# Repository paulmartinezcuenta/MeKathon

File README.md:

# 🤖 MeKathon - Autonomous Mini Sumo 10x10

Official team repository for the development of a fully autonomous Mini Sumo robot, designed to compete under the official rules of the 10x10 cm category.

## 📂 Project Structure

* 📁 [**`3D_Design/`**](./3D_Design): CAD models for the chassis, front scoop, and structural components.
* 📁 [**`PCB/`**](./PCB): Schematic design and PCB routing (KiCad).
* 📁 [**`Firmware/`**](./Firmware): C source code for control logic, sensor reading, and combat strategy implementation on the ESP32.
* 📁 [**`Docs/`**](./Docs): Official rules, component datasheets, and architecture diagrams.

## 🛠️ Engineering Specifications

| Subsystem | Description |
| :--- | :--- |
| **Microcontroller** | ESP32 |
| **Target Sensors** | [Specify model, e.g., Sharp IR / LiDAR] |
| **Edge Sensors** | [Specify model, e.g., QTR] |
| **Actuators** | High-speed micro metal gearmotors |
| **Power Supply** | LiPo Battery [e.g., 2S 7.4V] |

## 👥 Development Team
* **Paul** - Hardware & PCB Design
* **Miguel** - Structural 3D Design
* **Isaias** - Firmware Development
* **Alberto** - Firmware Development

---
*Designed for the MeKathon 2026 competition.*

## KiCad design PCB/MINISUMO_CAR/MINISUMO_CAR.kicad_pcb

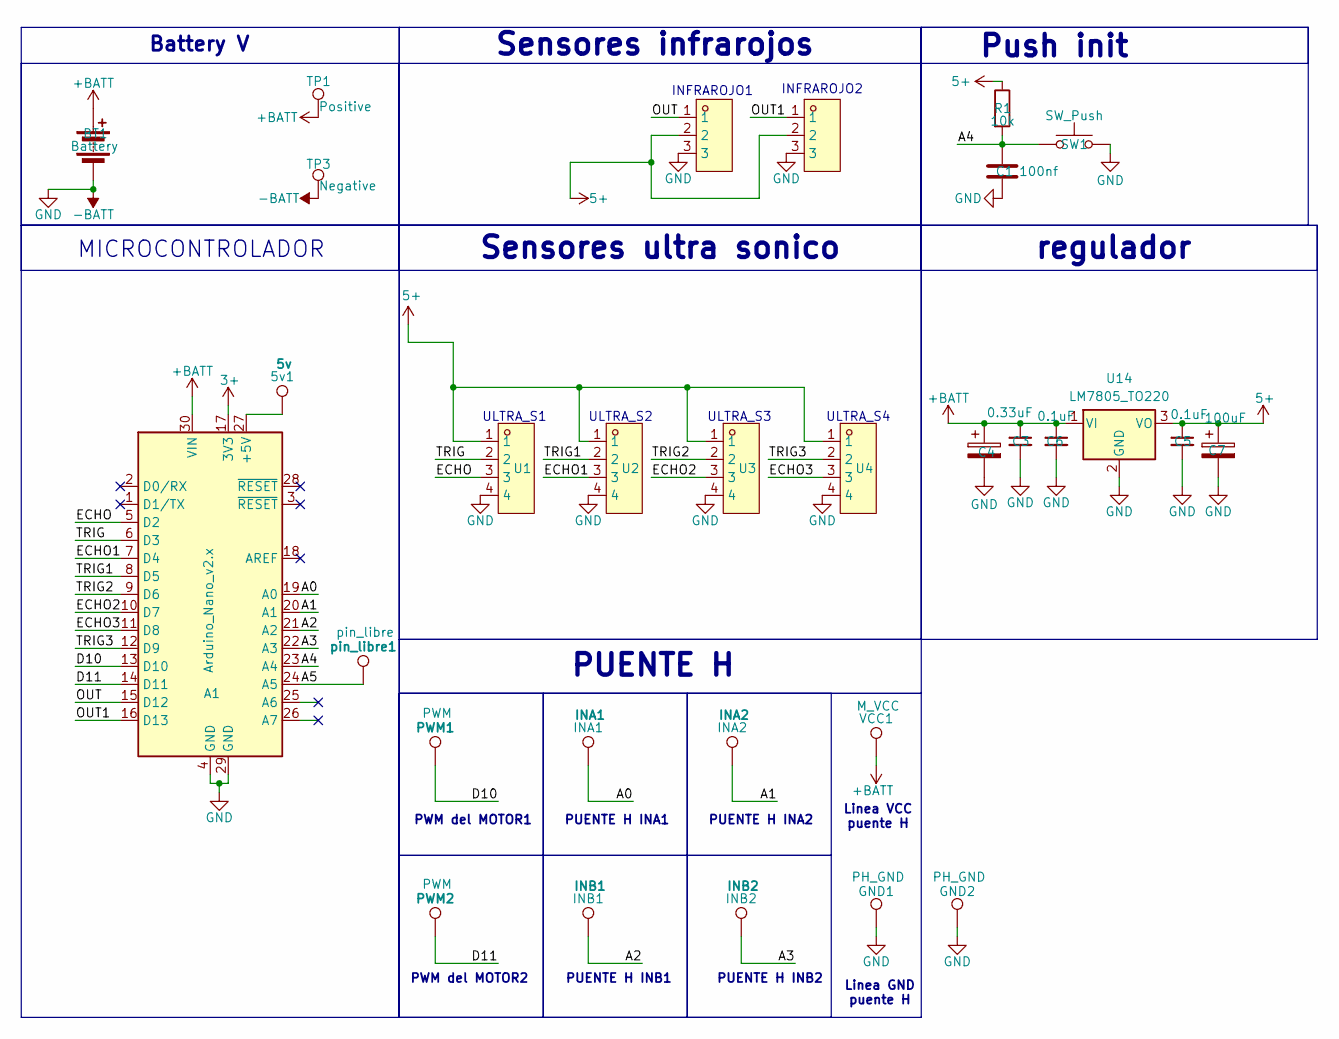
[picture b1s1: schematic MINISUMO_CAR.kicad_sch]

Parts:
5v1: 5v; PinHeader_1x01_P2.00mm_Vertical
A1: Arduino_Nano_v2.x; Arduino_Nano
BT1: Battery
C1: 100nf; C_0805_2012Metric
C3: 0.33uF; C_0805_2012Metric
C4: 470uf; CP_Elec_10x10.5
C5, C6: 0.1uF; C_0805_2012Metric
C7: 100uF; CP_Elec_6.3x7.7
GND1, GND2: PH_GND; PinHeader_1x01_P2.00mm_Vertical
INA1: INA1; PinHeader_1x01_P2.00mm_Vertical
INA2: INA2; PinHeader_1x01_P2.00mm_Vertical
INB1: INB1; PinHeader_1x01_P2.00mm_Vertical
INB2: INB2; PinHeader_1x01_P2.00mm_Vertical
PWM1, PWM2: PWM; PinHeader_1x01_P2.00mm_Vertical
R1: 10k; R_0805_2012Metric_Pad1.20x1.40mm_HandSolder
SW1: SW_Push; SW_PUSH_6mm_H5mm
TP1: Positive; TestPoint_THTPad_3.0x3.0mm_Drill1.5mm
TP3: Negative; TestPoint_THTPad_3.0x3.0mm_Drill1.5mm
U1, U2, U3, U4: XY-XHB2.54-4A11; HDR-TH_4P-P2.50-V-F-2; MPN XY-XHB2.54-4A11; LCSC Part C19271388
U5, U6: XY-XHB2.54-3A11; CONN-TH_3P-P2.50_XY-XHB2.54-3A11; MPN XY-XHB2.54-3A11; LCSC Part C19271387
U14: LM7805_TO220; TO-220-3_Vertical
VCC1: M_VCC; PinHeader_1x01_P2.00mm_Vertical
pin_libre1: pin_libre; PinHeader_1x01_P2.00mm_Vertical

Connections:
3+: A1.17 (3V3)
5+: C5.1, C7.1, R1.1, U1.1, U2.1, U3.1, U4.1, U5.2, U6.2, U14.3 (VO)
+BATT: A1.30 (VIN), BT1.1 (+), C3.1, C4.1, C6.1, TP1.1 (1_1), U14.1 (VI), VCC1.1 (1_1)
-BATT: A1.4 (GND), A1.29 (GND), BT1.2 (-), C1.2, C3.2, C4.2, C5.2, C6.2, C7.2, GND1.1 (1_1), GND2.1 (1_1), SW1.2, TP3.1 (1_1), U1.4, U2.4, U3.4, U4.4, U5.3, U6.3, U14.2 (GND); also elsewhere on the board
/A0: A1.19 (A0), INA1.1 (1_1)
/A1: A1.20 (A1), INA2.1 (1_1)
/A2: A1.21 (A2), INB1.1 (1_1)
/A3: A1.22 (A3), INB2.1 (1_1)
/A4: A1.23 (A4), C1.1, R1.2, SW1.1
/A5: A1.24 (A5), pin_libre1.1 (1_1)
/D10: A1.13 (D10), PWM1.1 (1_1)
/D11: A1.14 (D11), PWM2.1 (1_1)
/ECHO: A1.5 (D2), U1.3
/ECHO1: A1.7 (D4), U2.3
/ECHO2: A1.10 (D7), U3.3
/ECHO3: A1.11 (D8), U4.3
/OUT: A1.15 (D12), U5.1
/OUT1: A1.16 (D13), U6.1
/TRIG: A1.6 (D3), U1.2
/TRIG1: A1.8 (D5), U2.2
/TRIG2: A1.9 (D6), U3.2
/TRIG3: A1.12 (D9), U4.2
unnamed: 5v1.1 (1_1), A1.27 (+5V)

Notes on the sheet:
Sensores ultra sonico
ULTRA_S4
ULTRA_S1
PUENTE H
PUENTE H INB1
regulador
Battery V
Sensores infrarojos
INFRAROJO1
PUENTE H INA2
Linea GND puente H
PUENTE H INA1
ULTRA_S2
ULTRA_S3
Linea VCC puente H
Push init
INFRAROJO2
MICROCONTROLADOR
PWM del MOTOR2
PWM del MOTOR1
PUENTE H INB2

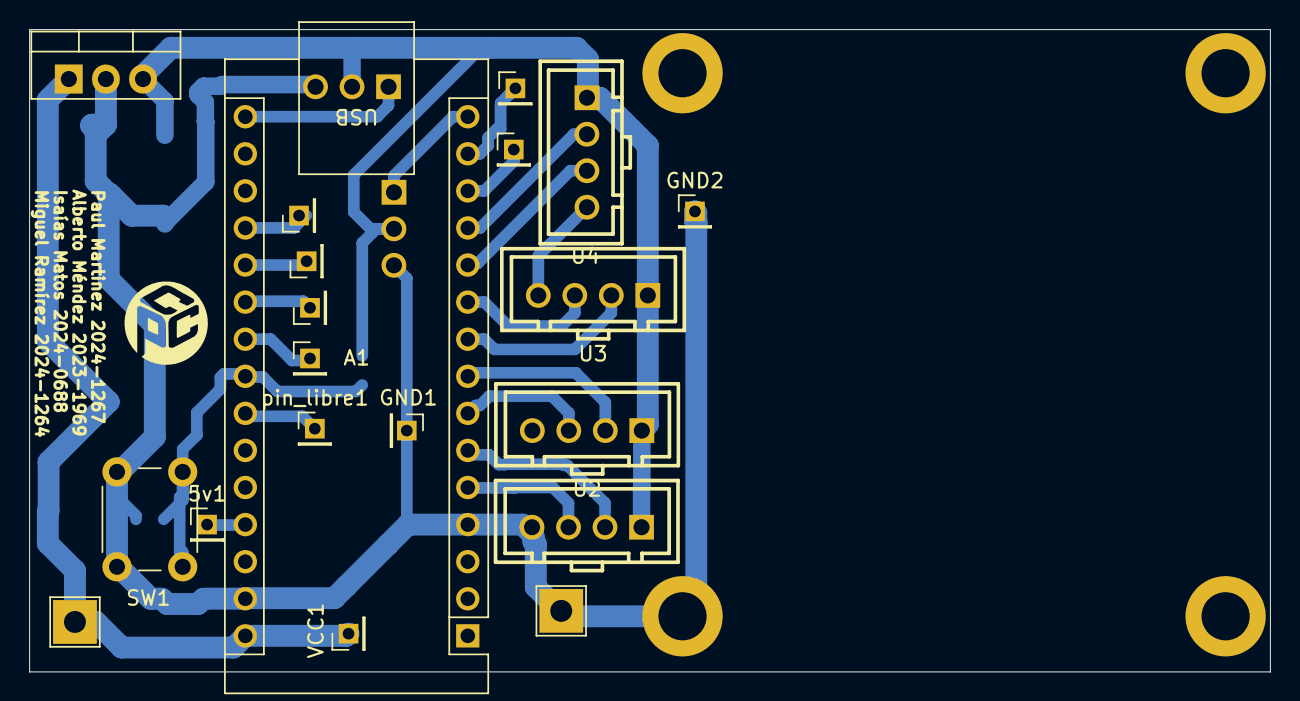
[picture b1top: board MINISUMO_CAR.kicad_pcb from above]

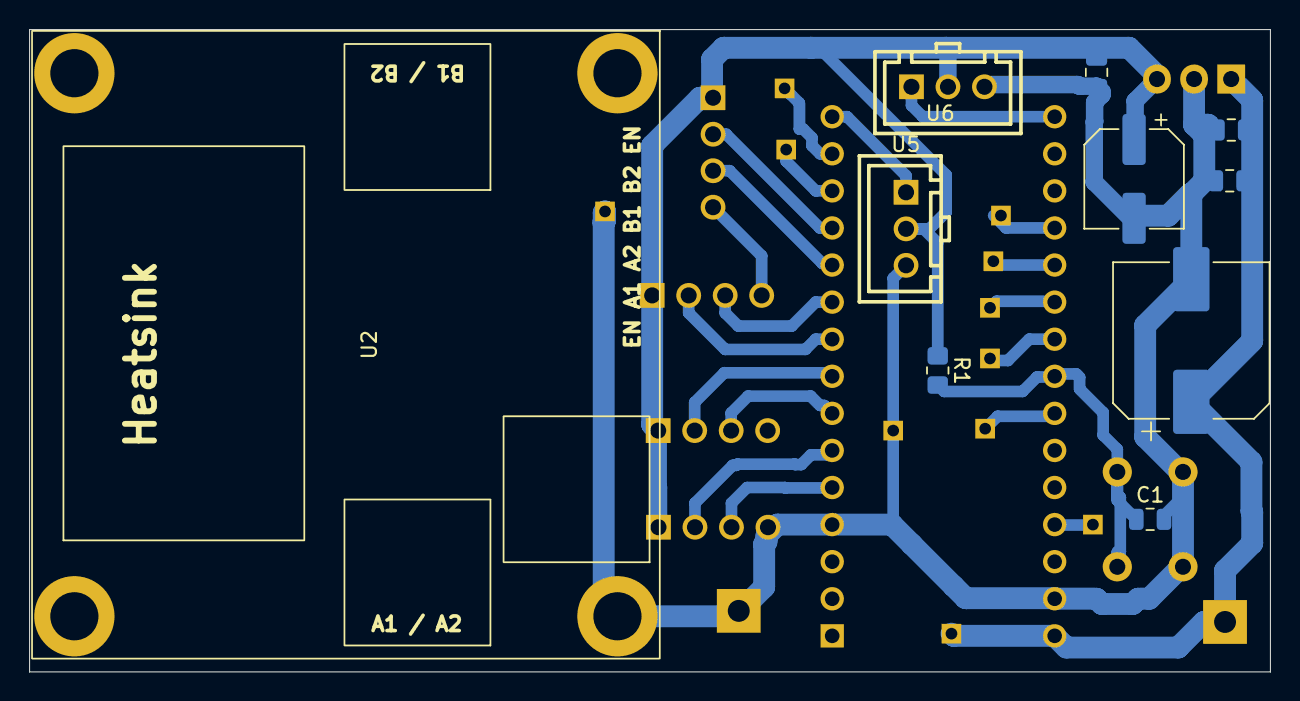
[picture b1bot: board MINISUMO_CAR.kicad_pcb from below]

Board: 2 copper layers, 85.0 x 44.0 mm, 31 parts (10 on the bottom side), 22 nets.

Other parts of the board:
THECPCENTER: LOGO; IMG1
U2#2: L298N; L298N-module-43x43mm

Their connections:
-BATT: U2#2.1; also elsewhere on the board
